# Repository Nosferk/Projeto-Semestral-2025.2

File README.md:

# Projeto-Semestral-2025.2

[Kitcat](https://kicanvas.org/?github=https%3A%2F%2Fgithub.com%2FNosferk%2FProjeto-Semestral-2025.2%2Fblob%2Fmain%2Fkitcat%2Fkitcat.kicad_sch)

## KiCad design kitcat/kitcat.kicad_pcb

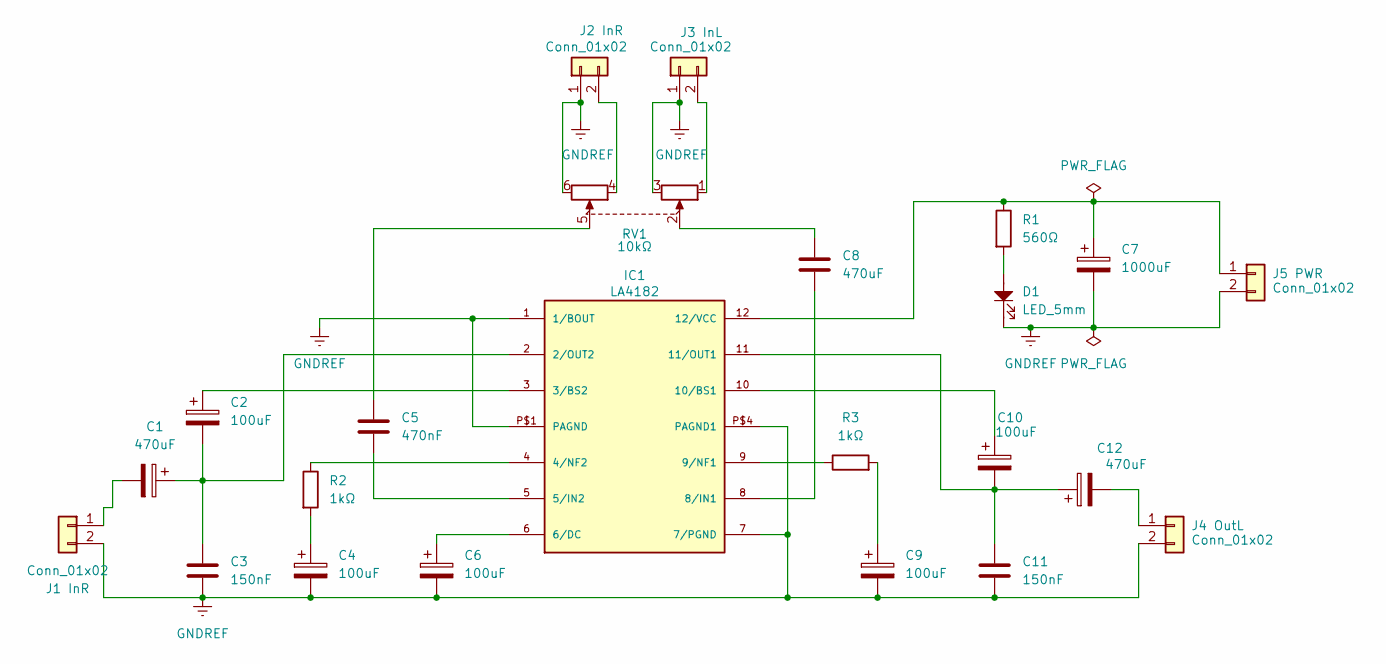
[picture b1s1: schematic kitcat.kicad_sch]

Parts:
C1, C12: 470uF; Capacitor_Eletrolítico_7.5mm
C2, C4, C6, C9, C10: 100uF; Capacitor_Eletrolítico_5mm
C3, C11: 150nF; Capacitor_Poliesterp
C5: 470nF; Capacitor_Poliesterg
C7: 1000uF; Capacitor_Eletrolítico_10mm
C8: 470uF; Capacitor_Poliesterg
D1: LED_5mm; Led_5mm
IC1: LA4182; Circuito integrado
J1 InR, J2 InR, J3 InL, J4 OutL, J5 PWR: Conn_01x02; Conector KRE
R1: 560Ω; Resistor_220_1_4W
R2, R3: 1kΩ; Resistor_1_4W
RV1: 10kΩ; Potenciometro_dual

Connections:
GNDREF: C3.2, C4.2, C6.2, C7.2, C9.2, C11.2, D1.1, IC1.1 (1/BOUT), IC1.7 (7/PGND), IC1.P$1 (PAGND), IC1.P$4 (PAGND1), J1 InR.2, J2 InR.1, J3 InL.1, J4 OutL.2, J5 PWR.2, RV1.3, RV1.6
unnamed: C4.1, R2.2
unnamed: C5.1, RV1.5
unnamed: C8.1, RV1.2
unnamed: C9.1, R3.2
unnamed: D1.2, R1.2
unnamed: C1.1, C2.2, C3.1, IC1.2 (2/OUT2)
unnamed: C2.1, IC1.3 (3/BS2)
unnamed: IC1.4 (4/NF2), R2.1
unnamed: C5.2, IC1.5 (5/IN2)
unnamed: C6.1, IC1.6 (6/DC)
unnamed: C8.2, IC1.8 (8/IN1)
unnamed: IC1.9 (9/NF1), R3.1
unnamed: C10.1, IC1.10 (10/BS1)
unnamed: C10.2, C11.1, C12.1, IC1.11 (11/OUT1)
unnamed: C7.1, IC1.12 (12/VCC), J5 PWR.1, R1.1
unnamed: C1.2, J1 InR.1
unnamed: J2 InR.2, RV1.4
unnamed: J3 InL.2, RV1.1
unnamed: C12.2, J4 OutL.1

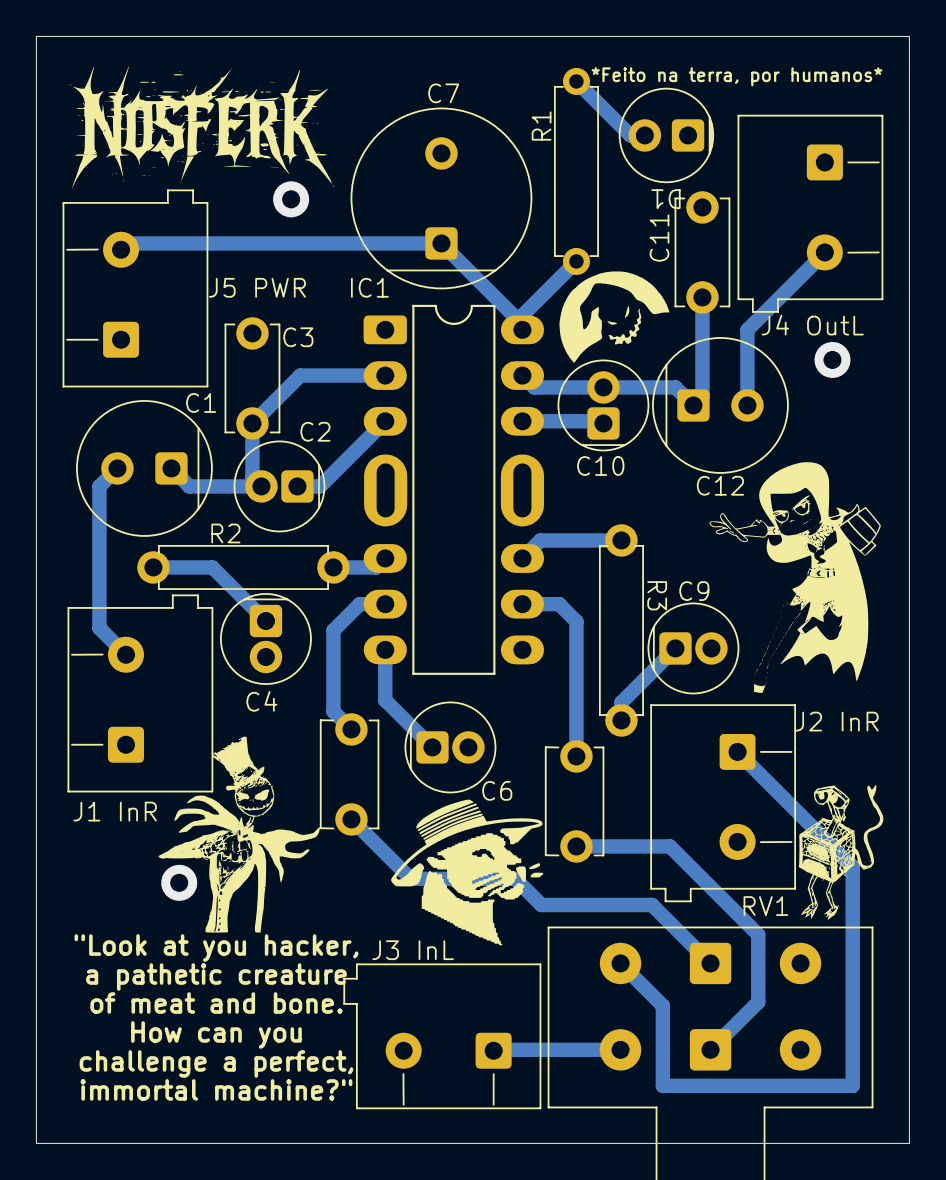
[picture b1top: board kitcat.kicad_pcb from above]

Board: 2 copper layers, 48.5 x 61.5 mm, 23 parts (0 on the bottom side), 20 nets.

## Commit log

2025-06-13 sferrargfrg
2025-06-18 Proteus
2025-06-19 23546
2025-06-20 aaaaa
2025-06-20 s5x7y
2025-06-23 wykyrkm4u4yj67k6e4aytj64tj3uah
2025-07-09 hterhytnnnytjjyjnyt
2025-07-12 wrth
2025-07-14 aerg
2025-07-14 wsderg
2025-07-14 Update via position in PCB and remove lock fil
    Adjusted the position of a via in kitcat.kicad_pcb for layout refinement. Deleted the temporary schematic lock file ~kitcat.kicad_sch.lck.
2025-07-14 Ultimo commit da noite
